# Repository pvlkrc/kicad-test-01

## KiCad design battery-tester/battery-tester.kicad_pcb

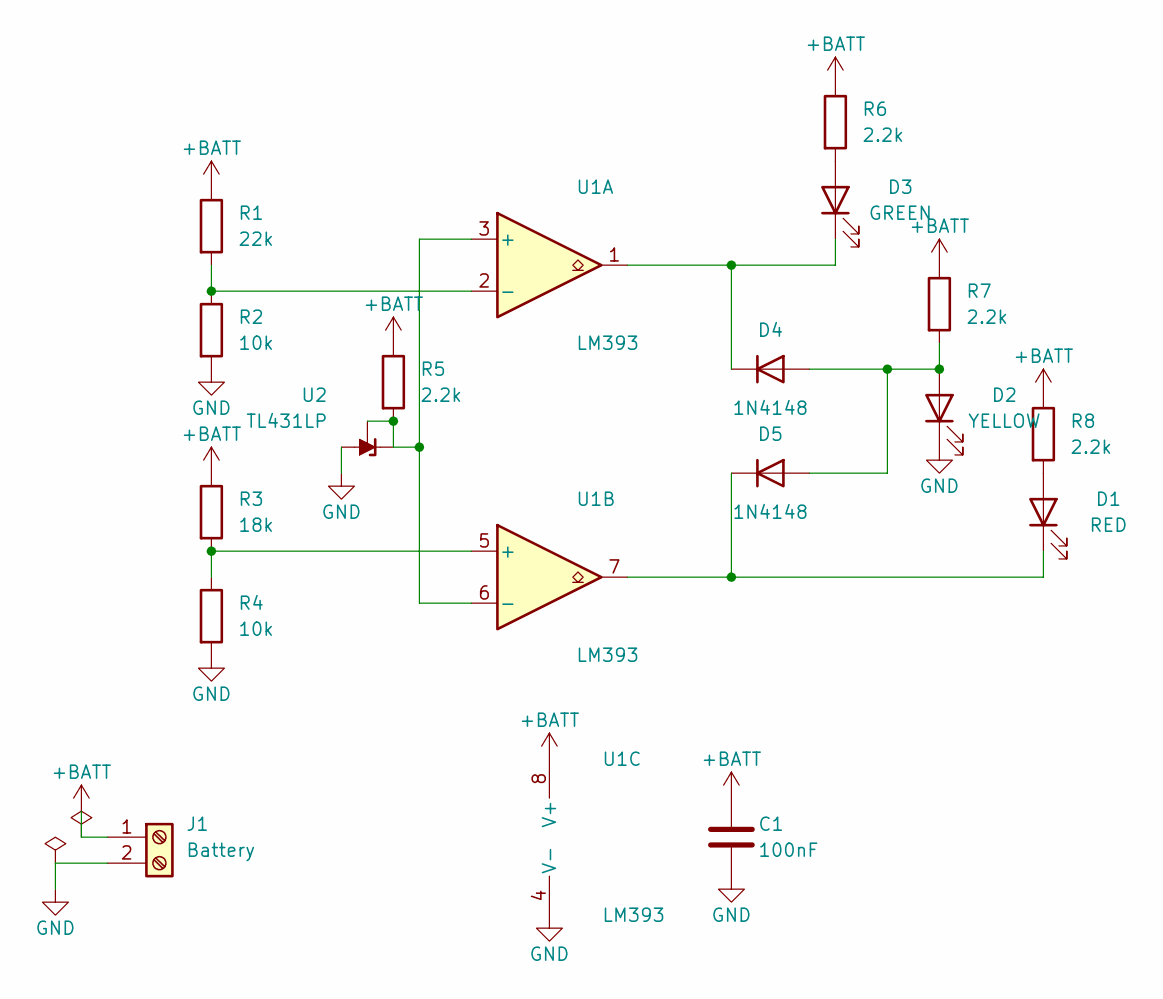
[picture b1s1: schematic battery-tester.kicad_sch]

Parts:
C1: 100nF; C_Disc_D5.0mm_W2.5mm_P5.00mm
D1: RED; LED_D5.0mm
D2: YELLOW; LED_D5.0mm
D3: GREEN; LED_D5.0mm
D4, D5: 1N4148; D_DO-35_SOD27_P7.62mm_Horizontal
J1: Battery; TerminalBlock_Phoenix_MKDS-1,5-2_1x02_P5.00mm_Horizontal
R1: 22k; R_Axial_DIN0207_L6.3mm_D2.5mm_P7.62mm_Horizontal
R2, R4: 10k; R_Axial_DIN0207_L6.3mm_D2.5mm_P7.62mm_Horizontal
R3: 18k; R_Axial_DIN0207_L6.3mm_D2.5mm_P7.62mm_Horizontal
R5, R6, R7, R8: 2.2k; R_Axial_DIN0207_L6.3mm_D2.5mm_P7.62mm_Horizontal
U1: LM393; DIP-8_W7.62mm
U2: TL431LP; TO-92_Inline

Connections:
+BATT: C1.1, J1.1, R1.1, R3.1, R5.1, R6.1, R7.1, R8.1, U1.8 (V+)
GND: C1.2, D2.1 (K), J1.2, R2.2, R4.2, U1.4 (V-), U2.2 (A)
unnamed: D1.2 (A), R8.2
unnamed: D1.1 (K), D5.1 (K), U1.7
unnamed: D2.2 (A), D4.2 (A), D5.2 (A), R7.2
unnamed: D3.2 (A), R6.2
unnamed: D3.1 (K), D4.1 (K), U1.1
unnamed: R5.2, U1.3 (+), U1.6 (-), U2.1 (REF), U2.3 (K)
unnamed: R1.2, R2.1, U1.2 (-)
unnamed: R3.2, R4.1, U1.5 (+)

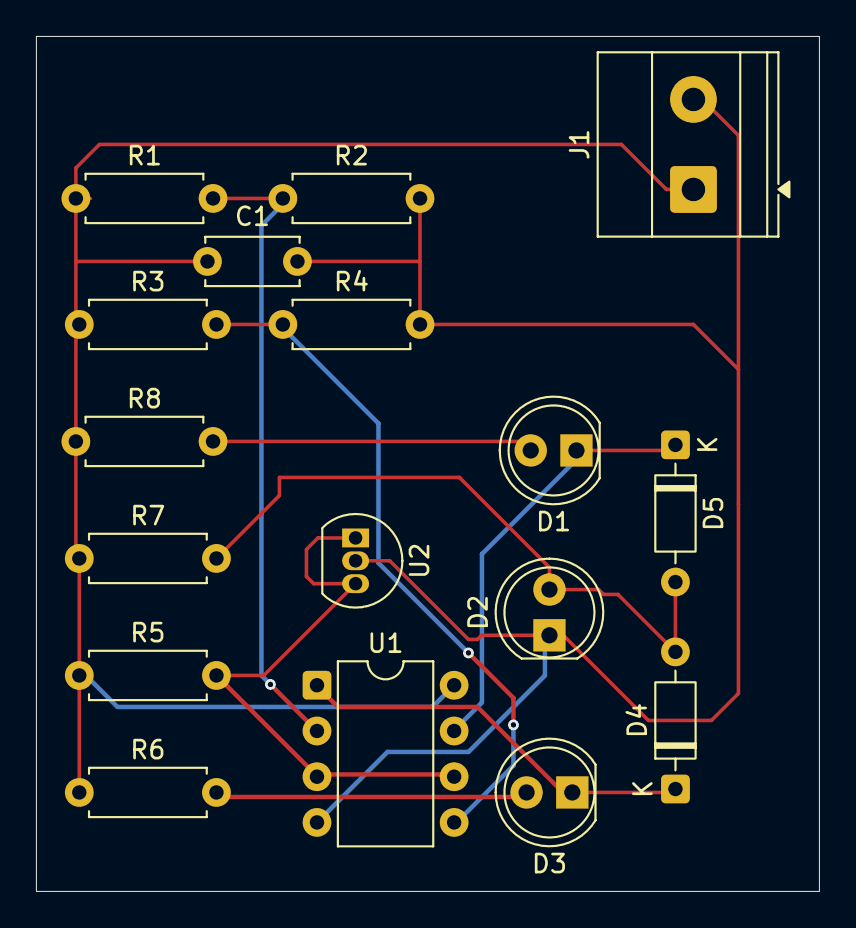
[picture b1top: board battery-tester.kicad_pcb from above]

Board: 2 copper layers, 43.5 x 47.5 mm, 17 parts (0 on the bottom side), 10 nets.

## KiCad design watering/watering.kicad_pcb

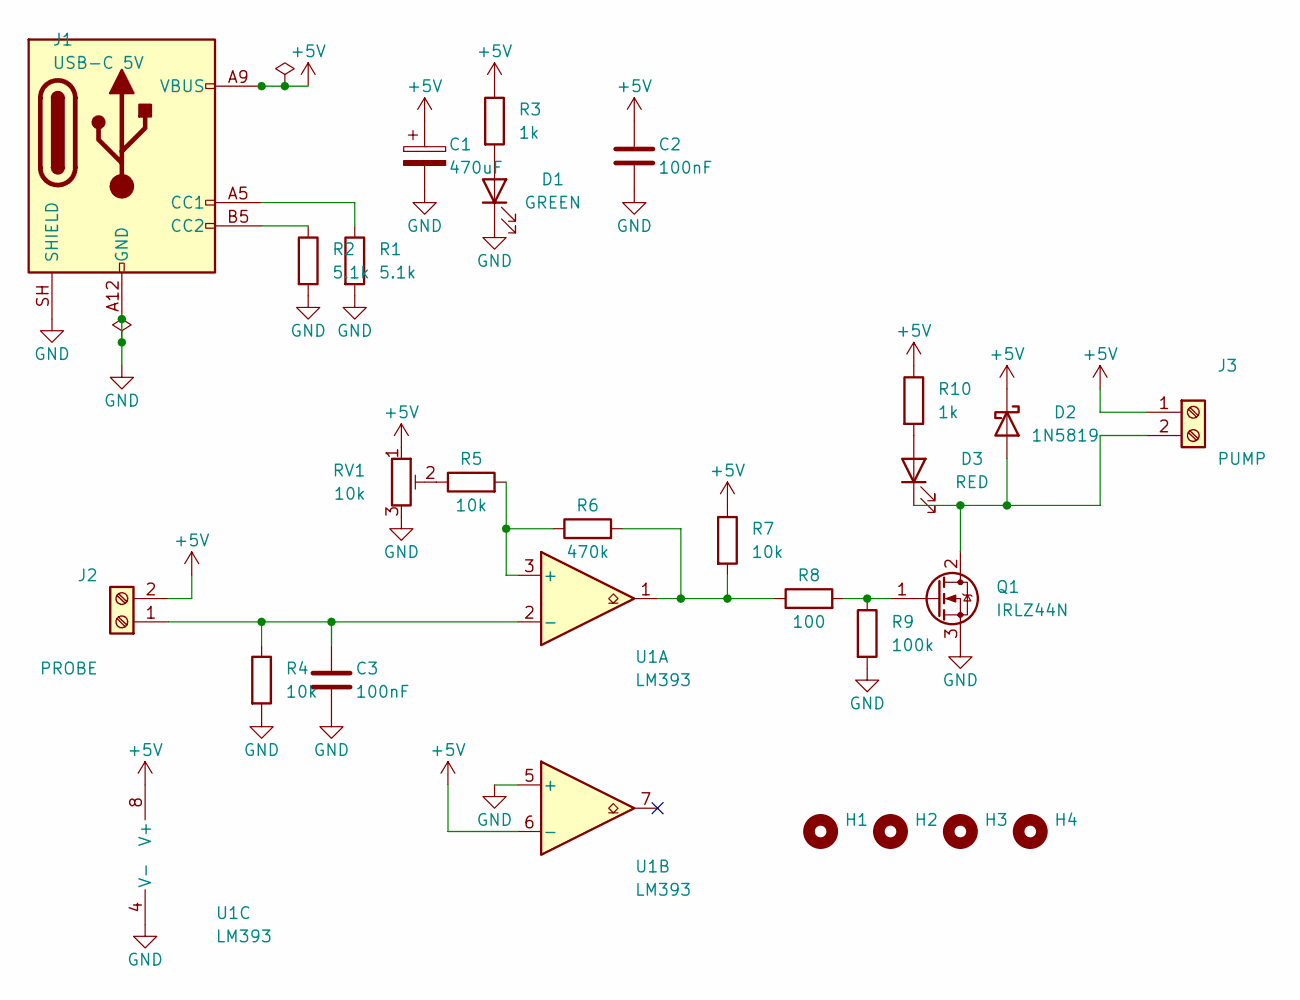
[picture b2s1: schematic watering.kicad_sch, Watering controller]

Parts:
C1: 470uF; CP_Radial_D8.0mm_P3.50mm
C2, C3: 100nF; C_Disc_D5.0mm_W2.5mm_P5.00mm
D1: GREEN; LED_D3.0mm
D2: 1N5819; D_DO-41_SOD81_P10.16mm_Horizontal
D3: RED; LED_D3.0mm
H1, H2, H3, H4: MountingHole; MountingHole_3.2mm_M3
J1: USB-C 5V; USB_C_Receptacle_GCT_USB4125-xx-x_6P_TopMnt_Horizontal
J2: PROBE; TerminalBlock_Phoenix_MKDS-1,5-2_1x02_P5.00mm_Horizontal
J3: PUMP; TerminalBlock_Phoenix_MKDS-1,5-2_1x02_P5.00mm_Horizontal
Q1: IRLZ44N; TO-220-3_Vertical
R1, R2: 5.1k; R_Axial_DIN0207_L6.3mm_D2.5mm_P7.62mm_Horizontal
R3, R10: 1k; R_Axial_DIN0207_L6.3mm_D2.5mm_P7.62mm_Horizontal
R4, R5, R7: 10k; R_Axial_DIN0207_L6.3mm_D2.5mm_P7.62mm_Horizontal
R6: 470k; R_Axial_DIN0207_L6.3mm_D2.5mm_P7.62mm_Horizontal
R8: 100; R_Axial_DIN0207_L6.3mm_D2.5mm_P7.62mm_Horizontal
R9: 100k; R_Axial_DIN0207_L6.3mm_D2.5mm_P7.62mm_Horizontal
RV1: 10k; Potentiometer_Bourns_3386P_Vertical
U1: LM393; DIP-8_W7.62mm

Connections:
+5V: C1.1, C2.1, D2.1 (K), J1.A9 (VBUS), J1.B9 (VBUS), J2.2, J3.1, R3.1, R7.1, R10.1, RV1.1, U1.6 (-), U1.8 (V+)
GND: C1.2, C2.2, C3.2, D1.1 (K), J1.A12 (GND), J1.B12 (GND), J1.SH (SHIELD), Q1.3 (S), R1.2, R2.2, R4.2, R9.2, RV1.3, U1.4 (V-), U1.5 (+)
unnamed: D1.2 (A), R3.2
unnamed: D2.2 (A), D3.1 (K), J3.2, Q1.2 (D)
unnamed: D3.2 (A), R10.2
unnamed: J1.A5 (CC1), R1.1
unnamed: J1.B5 (CC2), R2.1
unnamed: C3.1, J2.1, R4.1, U1.2 (-)
unnamed: Q1.1 (G), R8.2, R9.1
unnamed: R5.1, RV1.2
unnamed: R6.2, R7.2, R8.1, U1.1
unnamed: R5.2, R6.1, U1.3 (+)

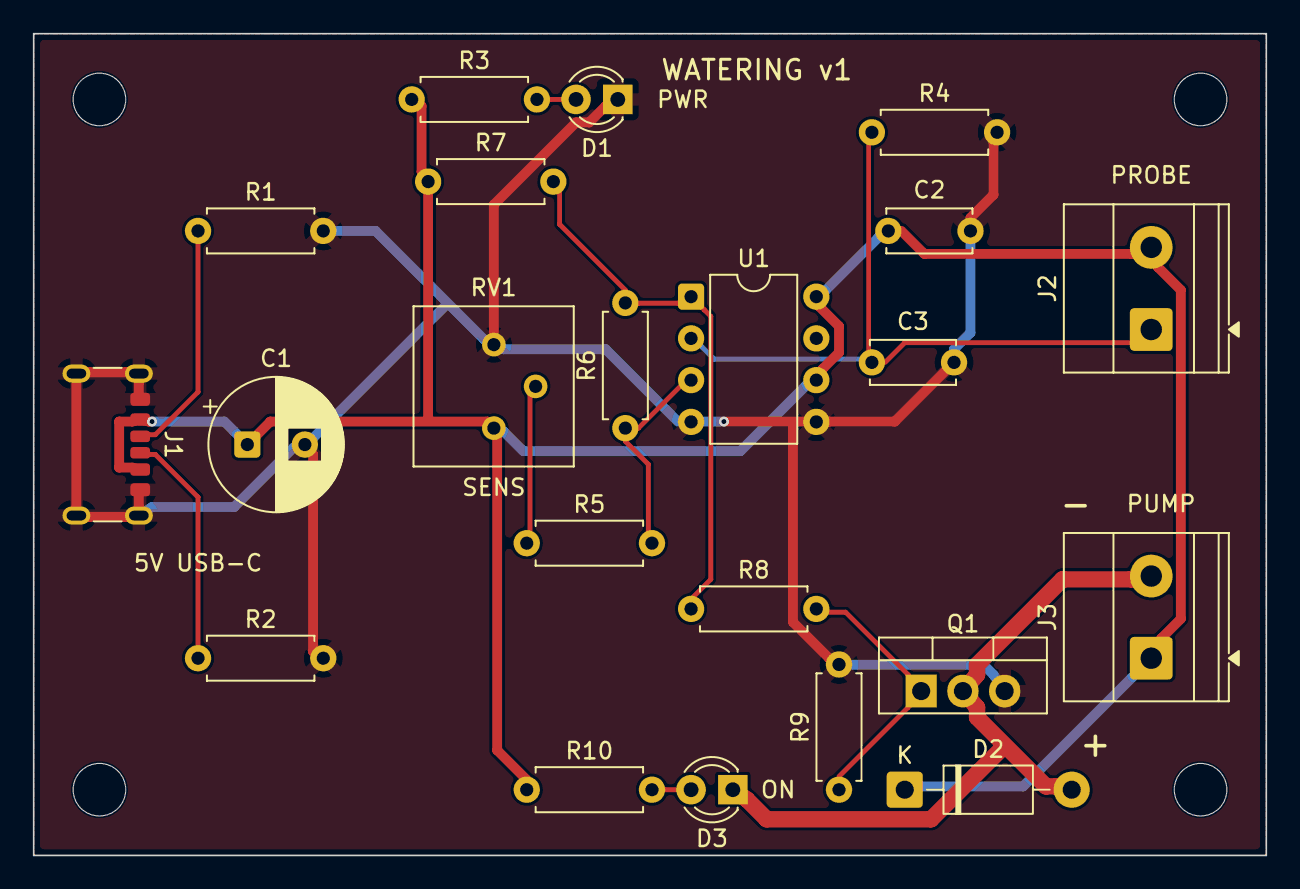
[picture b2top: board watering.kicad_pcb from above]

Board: 2 copper layers, 75.0 x 50.0 mm, 26 parts (0 on the bottom side), 12 nets.

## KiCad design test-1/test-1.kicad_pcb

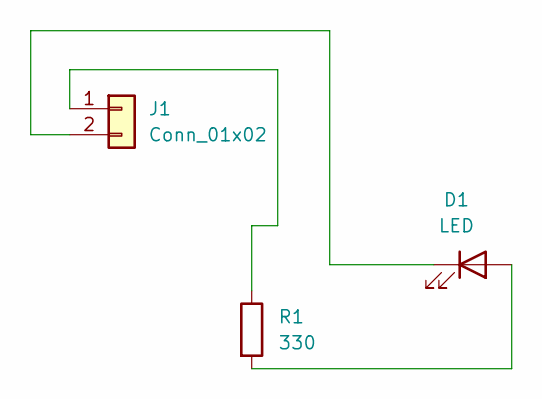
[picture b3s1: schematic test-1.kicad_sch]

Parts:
D1: LED; LED_D5.0mm
J1: Conn_01x02; PinHeader_1x02_P2.54mm_Vertical
R1: 330; R_Axial_DIN0207_L6.3mm_D2.5mm_P7.62mm_Horizontal

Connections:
unnamed: D1.2 (A), R1.2
unnamed: D1.1 (K), J1.2
unnamed: J1.1, R1.1

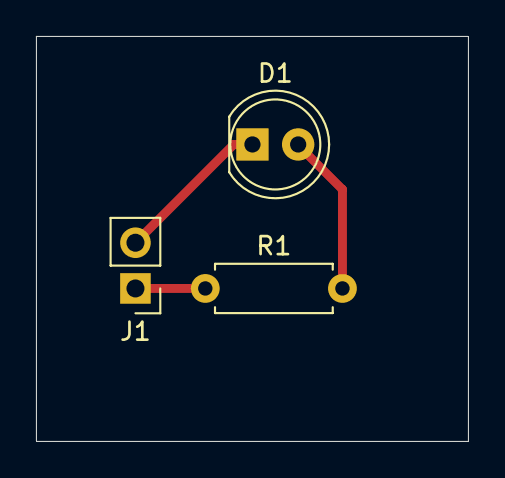
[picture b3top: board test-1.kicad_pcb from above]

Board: 2 copper layers, 24.0 x 22.5 mm, 3 parts (0 on the bottom side), 3 nets.
